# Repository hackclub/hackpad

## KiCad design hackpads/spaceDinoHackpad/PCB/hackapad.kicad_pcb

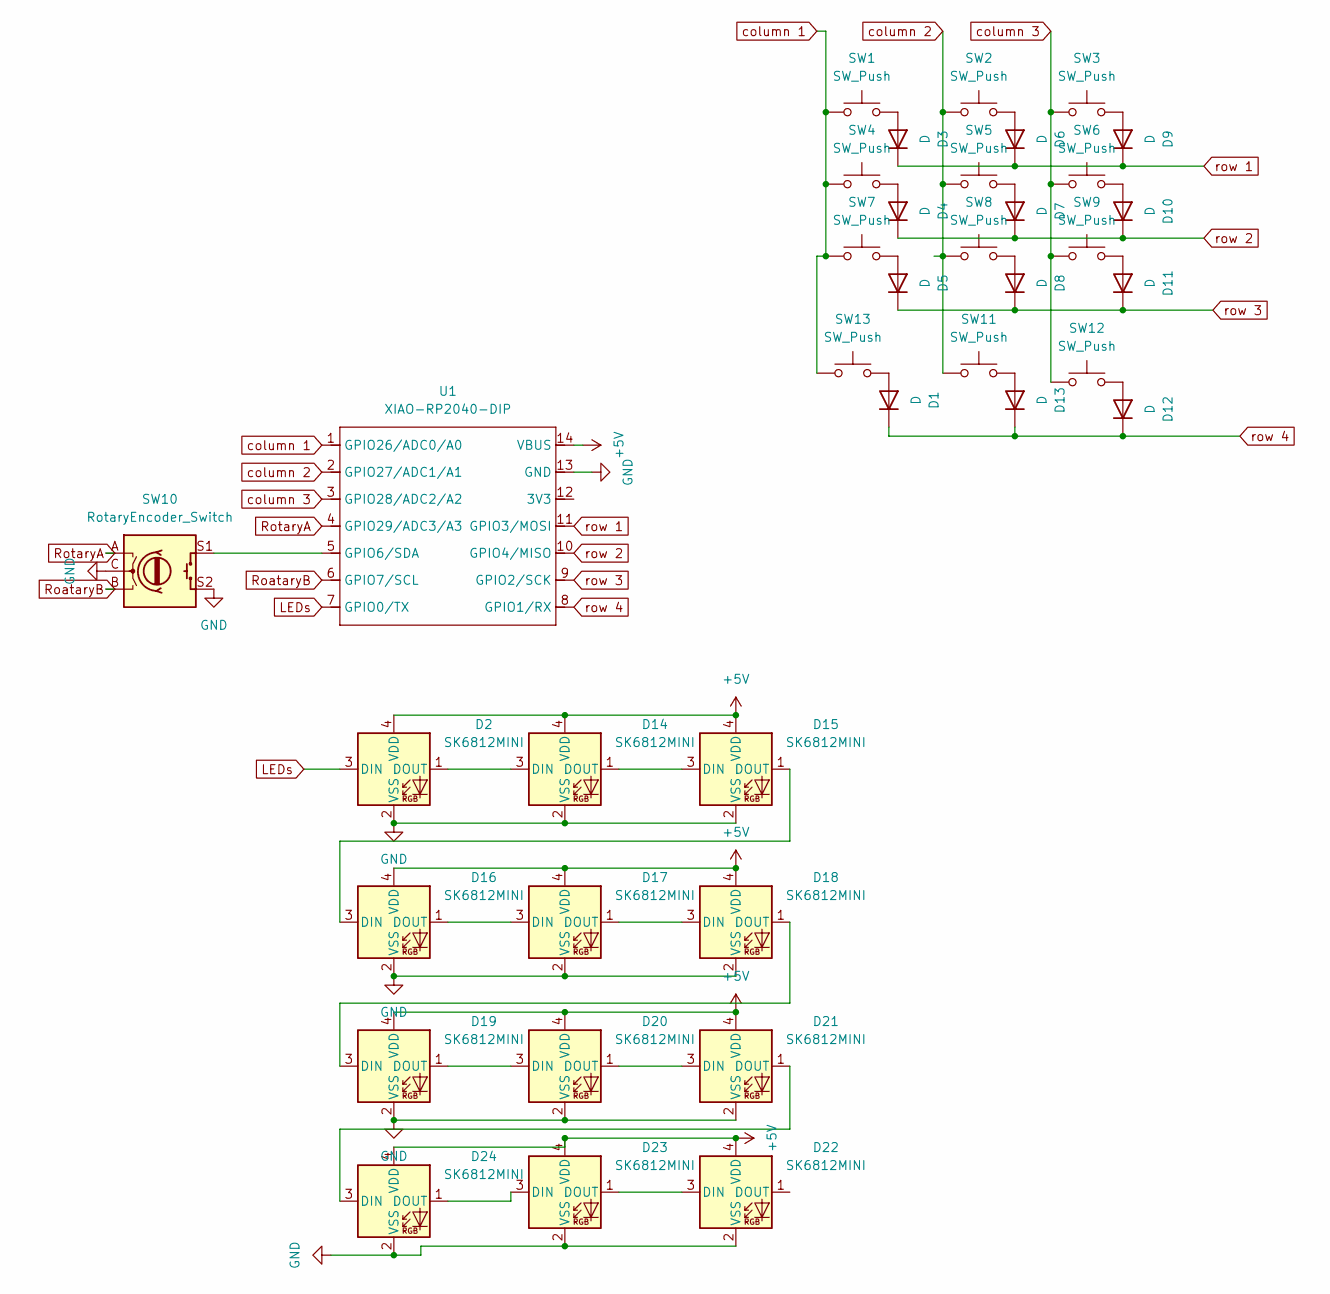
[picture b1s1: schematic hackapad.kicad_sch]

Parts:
D1, D3, D4, D5, D6, D7, D8, D9, D10, D11, D12, D13: D; D_DO-35_SOD27_P7.62mm_Horizontal
D2, D14, D15, D16, D17, D18, D19, D20, D21, D22, D23, D24: SK6812MINI; SK6812MINI-E
SW1, SW2, SW3, SW4, SW5, SW6, SW7, SW8, SW9, SW11, SW12, SW13: SW_Push; SW_Cherry_MX_1.00u_PCB_copy
SW10: RotaryEncoder_Switch; RotaryEncoder_Alps_EC11E-Switch_Vertical_H20mm_CircularMoun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
U1: XIAO-RP2040-DIP

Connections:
+5V: D2.4 (VDD), D14.4 (VDD), D15.4 (VDD), D16.4 (VDD), D17.4 (VDD), D18.4 (VDD), D19.4 (VDD), D20.4 (VDD), D21.4 (VDD), D22.4 (VDD), D23.4 (VDD), D24.4 (VDD), U1.14 (VBUS)
GND: D2.2 (VSS), D14.2 (VSS), D15.2 (VSS), D16.2 (VSS), D17.2 (VSS), D18.2 (VSS), D19.2 (VSS), D20.2 (VSS), D21.2 (VSS), D22.2 (VSS), D23.2 (VSS), D24.2 (VSS), SW10.C, SW10.S2, U1.13 (GND)
LEDs: D2.3 (DIN), U1.7 (GPIO0/TX)
unnamed: D1.2 (A), SW13.2
unnamed: D3.2 (A), SW1.2
unnamed: D4.2 (A), SW4.2
unnamed: D5.2 (A), SW7.2
unnamed: D6.2 (A), SW2.2
unnamed: D7.2 (A), SW5.2
unnamed: D8.2 (A), SW8.2
unnamed: D9.2 (A), SW3.2
unnamed: D10.2 (A), SW6.2
unnamed: D11.2 (A), SW9.2
unnamed: D12.2 (A), SW12.2
unnamed: D13.2 (A), SW11.2
unnamed: D2.1 (DOUT), D14.3 (DIN)
unnamed: D14.1 (DOUT), D15.3 (DIN)
unnamed: D15.1 (DOUT), D16.3 (DIN)
unnamed: D16.1 (DOUT), D17.3 (DIN)
unnamed: D17.1 (DOUT), D18.3 (DIN)
unnamed: D18.1 (DOUT), D19.3 (DIN)
unnamed: D19.1 (DOUT), D20.3 (DIN)
unnamed: D20.1 (DOUT), D21.3 (DIN)
unnamed: D21.1 (DOUT), D24.3 (DIN)
unnamed: D22.3 (DIN), D23.1 (DOUT)
unnamed: D23.3 (DIN), D24.1 (DOUT)
unnamed: SW10.S1, U1.5 (GPIO6/SDA)
RoataryB: SW10.B, U1.6 (GPIO7/SCL)
RotaryA: SW10.A, U1.4 (GPIO29/ADC3/A3)
column 1: SW1.1, SW4.1, SW7.1, SW13.1, U1.1 (GPIO26/ADC0/A0)
column 2: SW2.1, SW5.1, SW8.1, SW11.1, U1.2 (GPIO27/ADC1/A1)
column 3: SW3.1, SW6.1, SW9.1, SW12.1, U1.3 (GPIO28/ADC2/A2)
row 1: D3.1 (K), D6.1 (K), D9.1 (K), U1.11 (GPIO3/MOSI)
row 2: D4.1 (K), D7.1 (K), D10.1 (K), U1.10 (GPIO4/MISO)
row 3: D5.1 (K), D8.1 (K), D11.1 (K), U1.9 (GPIO2/SCK)
row 4: D1.1 (K), D12.1 (K), D13.1 (K), U1.8 (GPIO1/RX)

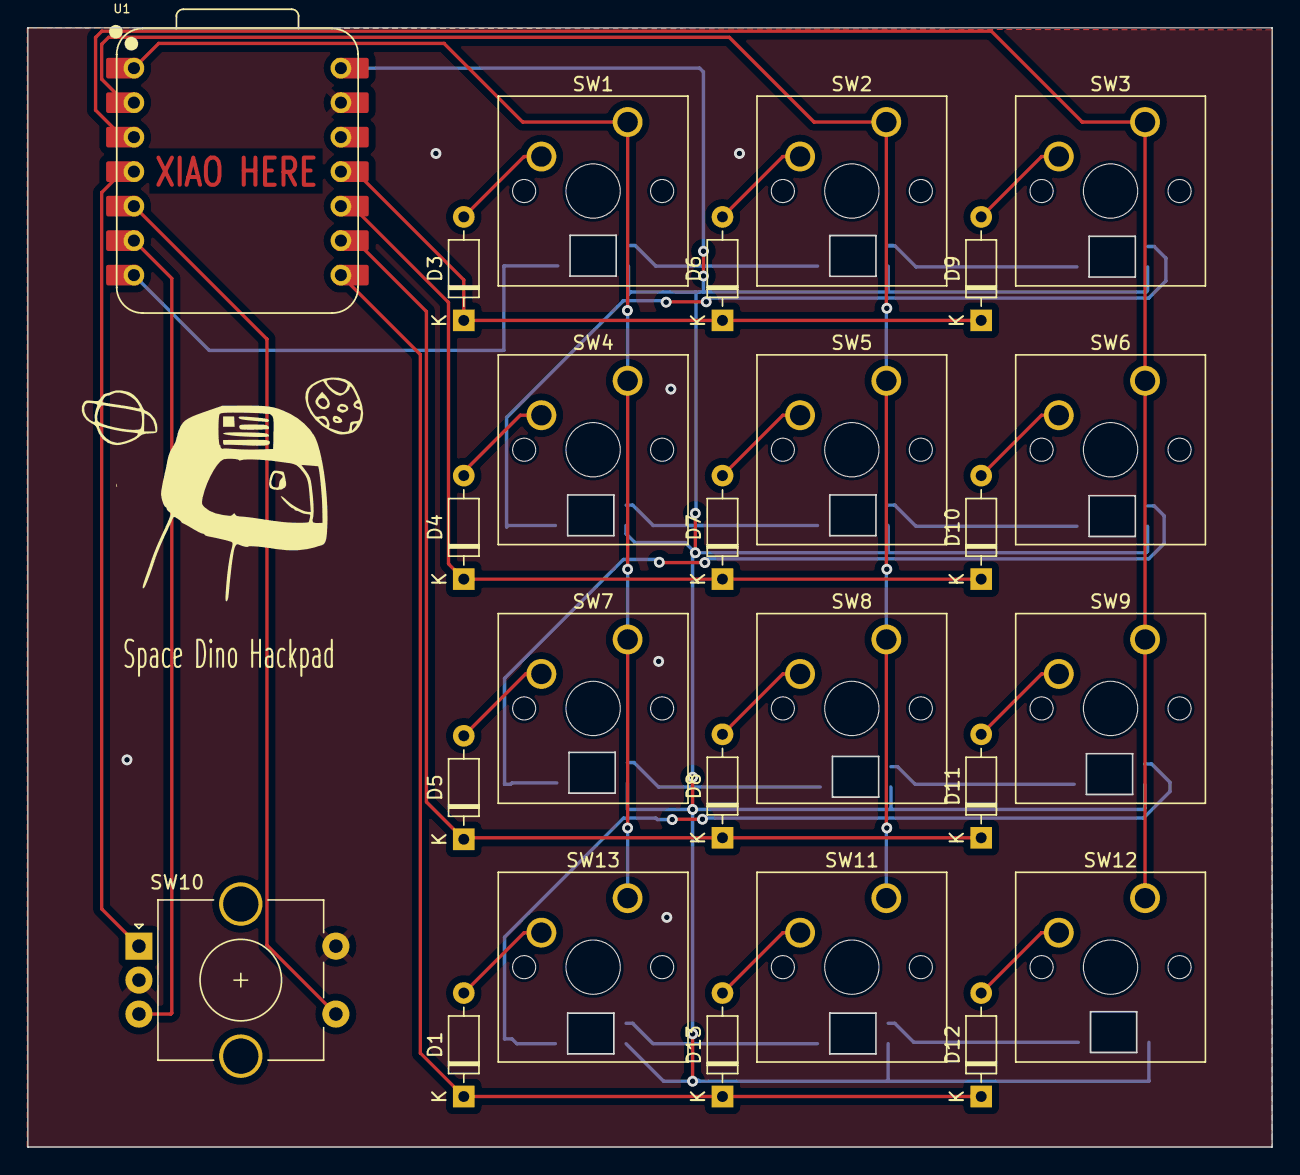
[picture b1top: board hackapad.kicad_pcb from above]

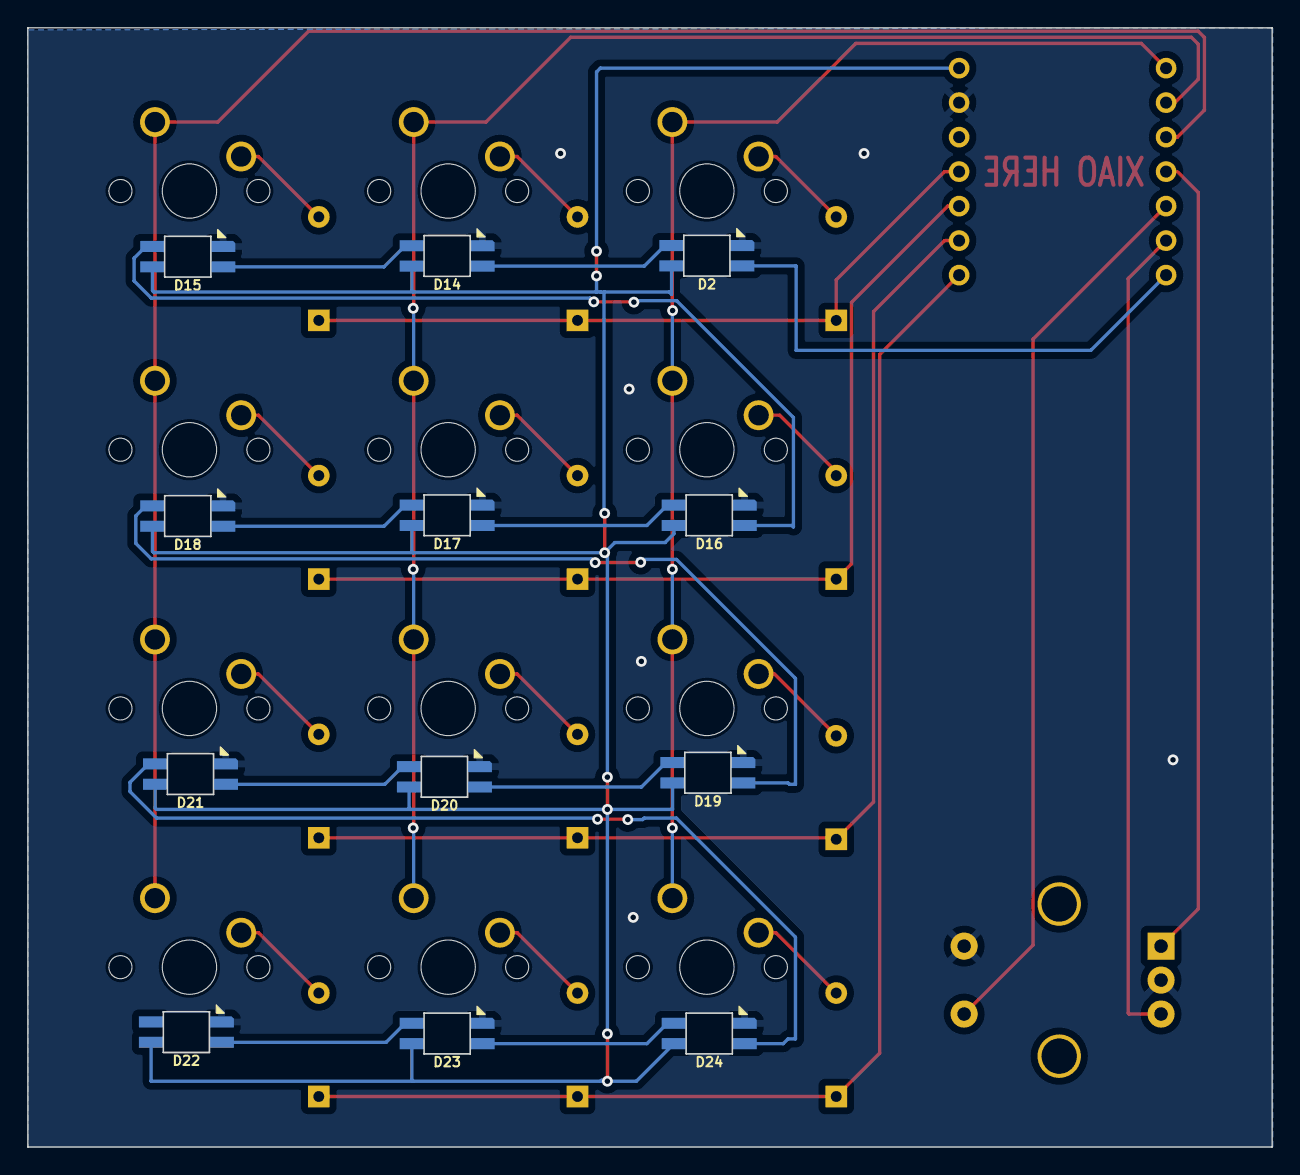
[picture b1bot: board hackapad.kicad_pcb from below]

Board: 2 copper layers, 91.6 x 82.4 mm, 38 parts (12 on the bottom side), 36 nets.

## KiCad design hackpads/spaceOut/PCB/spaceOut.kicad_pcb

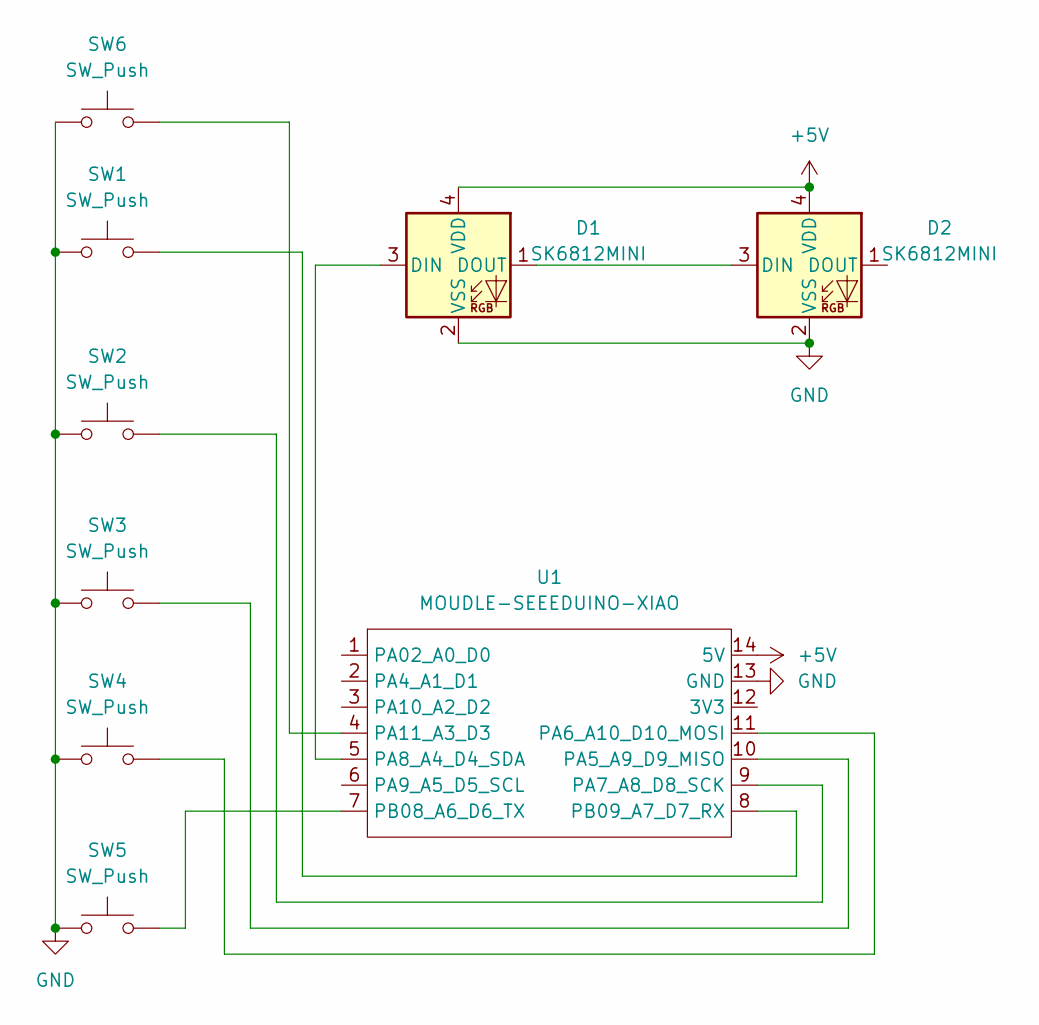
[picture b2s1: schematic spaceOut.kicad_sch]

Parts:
D1, D2: SK6812MINI; LED_SK6812MINI_PLCC4_3.5x3.5mm_P1.75mm
SW1, SW2, SW3, SW4, SW6: SW_Push; SW_Cherry_MX_1.00u_PCB
SW5: SW_Push; SW_Cherry_MX_2.75u_PCB
U1: MOUDLE-SEEEDUINO-XIAO; XIAO-SAMD21-RP2040-14P-2.54-21X17.8MM (Seeeduino XIAO)

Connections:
+5V: D1.4 (VDD), D2.4 (VDD), U1.14 (5V)
GND: D1.2 (VSS), D2.2 (VSS), SW1.1, SW2.1, SW3.1, SW4.1, SW5.1, SW6.1, U1.13 (GND)
unnamed: D1.3 (DIN), U1.5 (PA8_A4_D4_SDA)
unnamed: D1.1 (DOUT), D2.3 (DIN)
unnamed: SW3.2, U1.10 (PA5_A9_D9_MISO)
unnamed: SW4.2, U1.11 (PA6_A10_D10_MOSI)
unnamed: SW2.2, U1.9 (PA7_A8_D8_SCK)
unnamed: SW6.2, U1.4 (PA11_A3_D3)
unnamed: SW5.2, U1.7 (PB08_A6_D6_TX)
unnamed: SW1.2, U1.8 (PB09_A7_D7_RX)

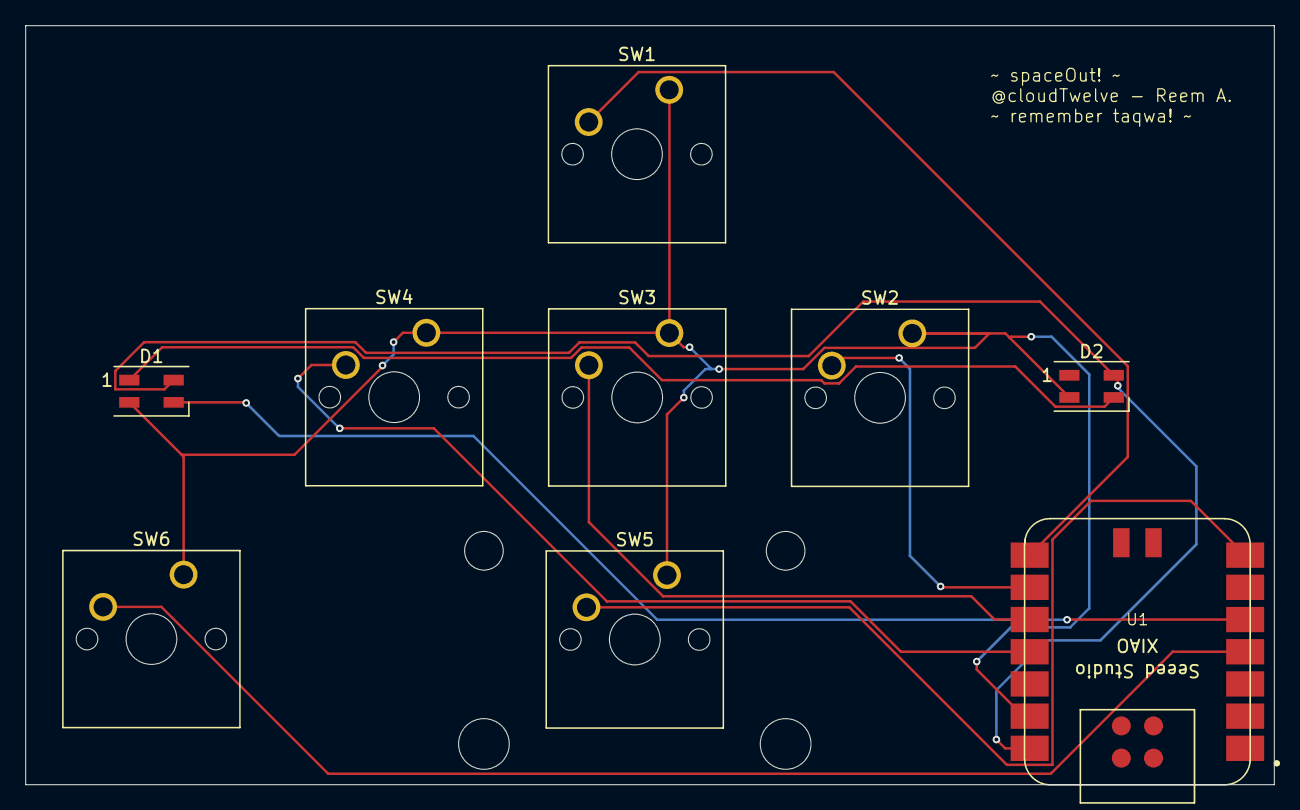
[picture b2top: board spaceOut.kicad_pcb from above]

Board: 2 copper layers, 98.5 x 59.9 mm, 9 parts (0 on the bottom side), 10 nets.

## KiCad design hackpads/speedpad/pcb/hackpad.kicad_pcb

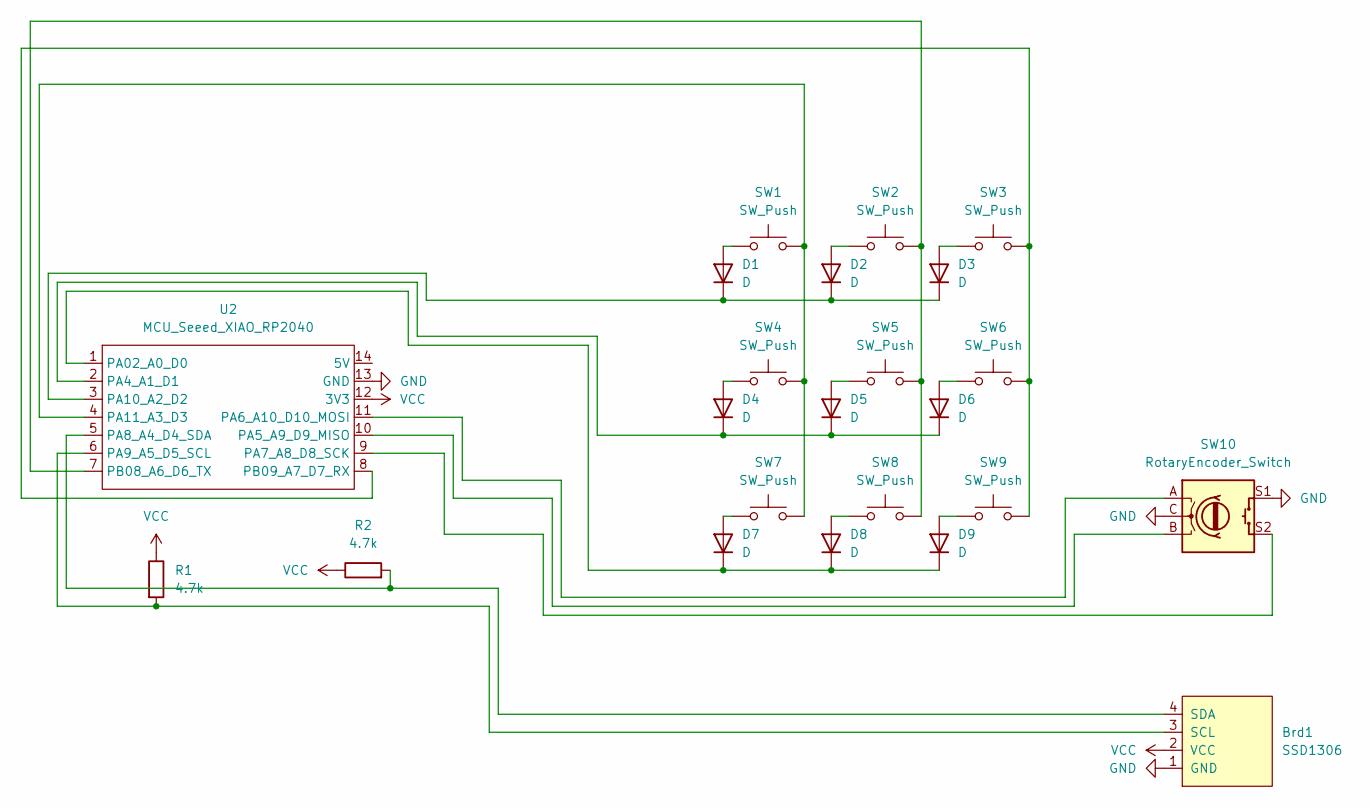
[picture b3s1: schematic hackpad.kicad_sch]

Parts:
Brd1: SSD1306; SSD1306-0.91-OLED-4pin-128x32
D1, D2, D3, D4, D5, D6, D7, D8, D9: D; DIODE-1N4148
R1, R2: 4.7k; R_Axial_DIN0204_L3.6mm_D1.6mm_P5.08mm_Horizontal
SW1, SW2, SW3, SW4, SW5, SW6, SW7, SW8, SW9: SW_Push; SW_Cherry_MX_1.00u_PCB
SW10: RotaryEncoder_Switch; RotaryEncoder_Alps_EC11E-Switch_Vertical_H20mm
U2: MCU_Seeed_XIAO_RP2040; XIAO-RP2040

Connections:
GND: Brd1.1 (GND), SW10.C, SW10.S1, U2.13 (GND)
unnamed: Brd1.3 (SCL), R1.2, U2.6 (PA9_A5_D5_SCL)
unnamed: Brd1.4 (SDA), R2.2, U2.5 (PA8_A4_D4_SDA)
unnamed: D1.A, SW1.1
unnamed: D2.A, SW2.1
unnamed: D3.A, SW3.1
unnamed: D4.A, SW4.1
unnamed: D5.A, SW5.1
unnamed: D6.A, SW6.1
unnamed: D7.A, SW7.1
unnamed: D8.A, SW8.1
unnamed: D9.A, SW9.1
unnamed: D7.K, D8.K, D9.K, U2.1 (PA02_A0_D0)
unnamed: D4.K, D5.K, D6.K, U2.2 (PA4_A1_D1)
unnamed: SW10.B, U2.10 (PA5_A9_D9_MISO)
unnamed: SW10.A, U2.11 (PA6_A10_D10_MOSI)
unnamed: SW10.S2, U2.9 (PA7_A8_D8_SCK)
unnamed: D1.K, D2.K, D3.K, U2.3 (PA10_A2_D2)
unnamed: SW1.2, SW4.2, SW7.2, U2.4 (PA11_A3_D3)
unnamed: SW2.2, SW5.2, SW8.2, U2.7 (PB08_A6_D6_TX)
unnamed: SW3.2, SW6.2, SW9.2, U2.8 (PB09_A7_D7_RX)
VCC: Brd1.2 (VCC), R1.1, R2.1, U2.12 (3V3)

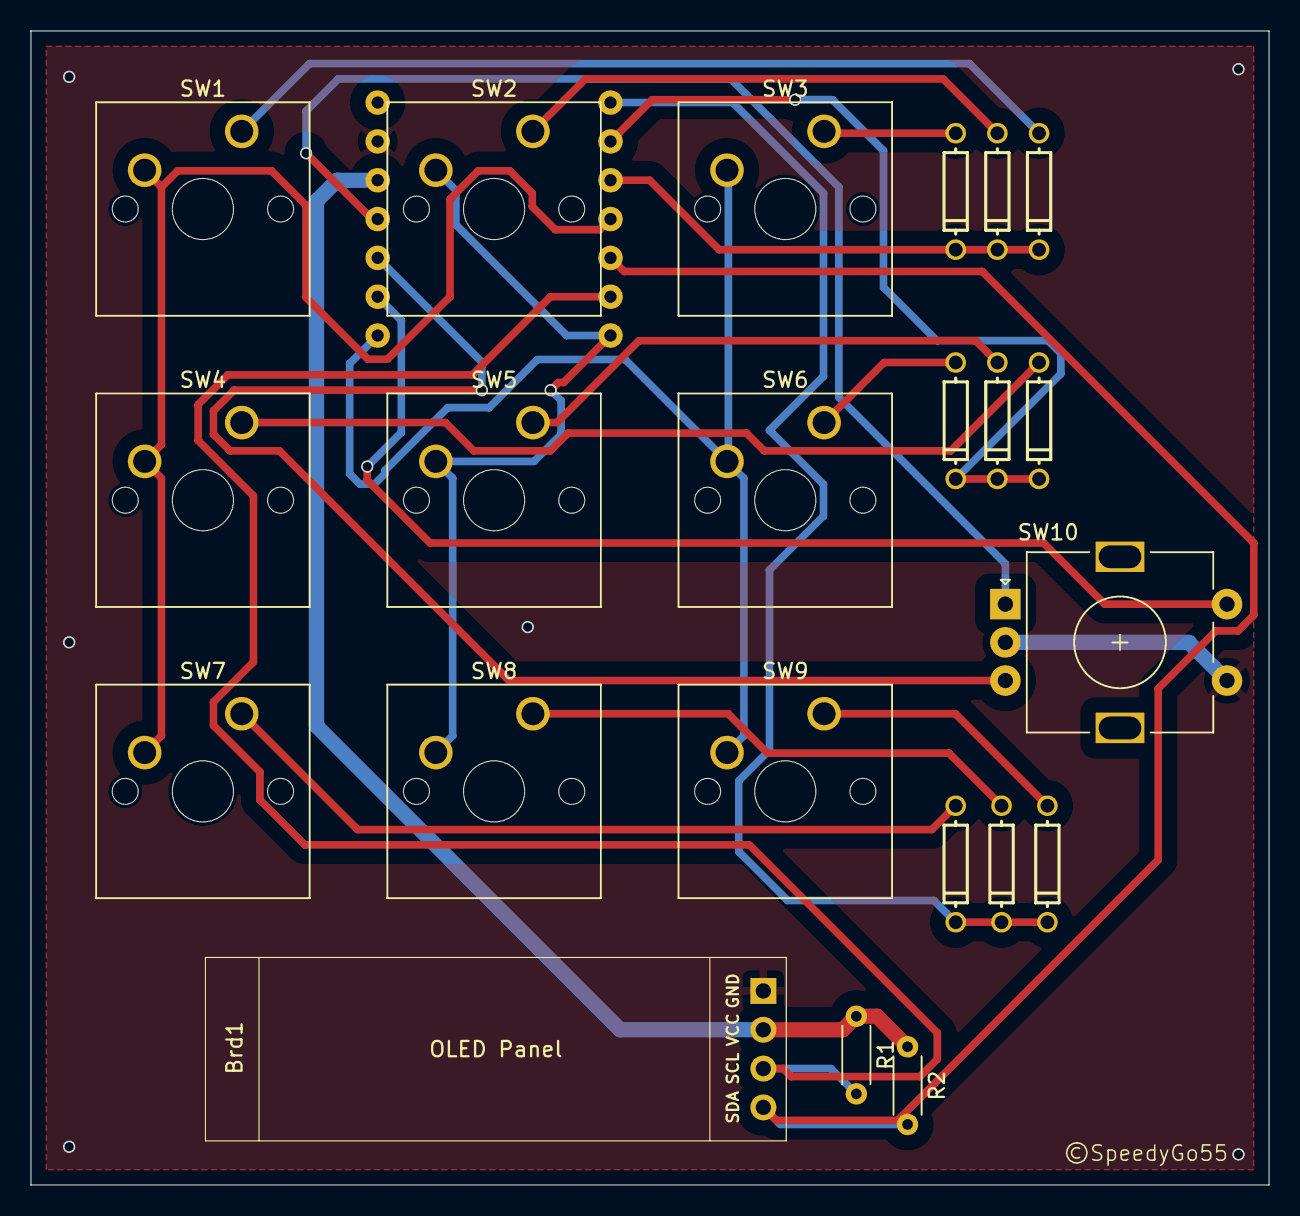
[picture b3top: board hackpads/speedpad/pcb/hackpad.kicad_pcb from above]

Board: 2 copper layers, 81.0 x 75.5 mm, 23 parts (1 on the bottom side), 22 nets.

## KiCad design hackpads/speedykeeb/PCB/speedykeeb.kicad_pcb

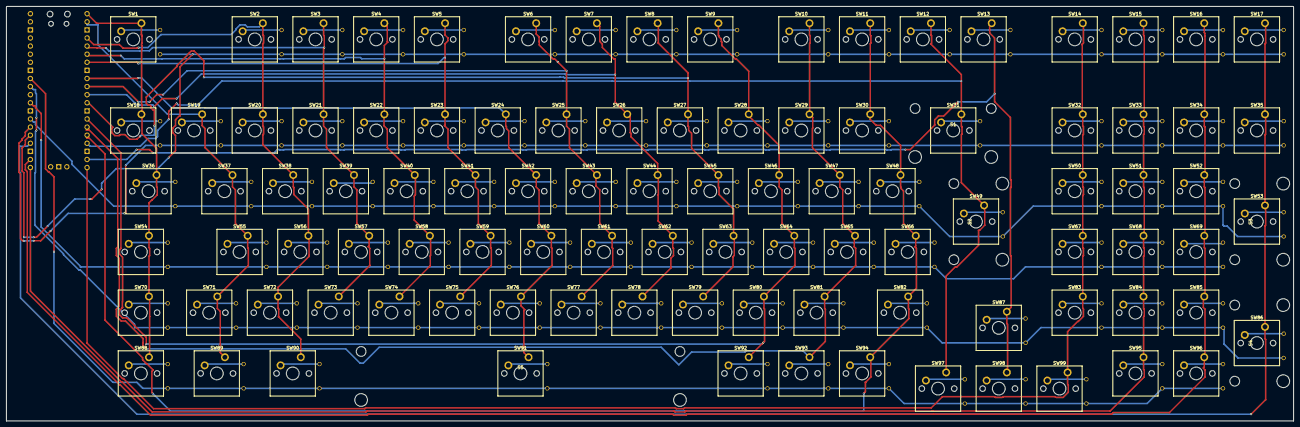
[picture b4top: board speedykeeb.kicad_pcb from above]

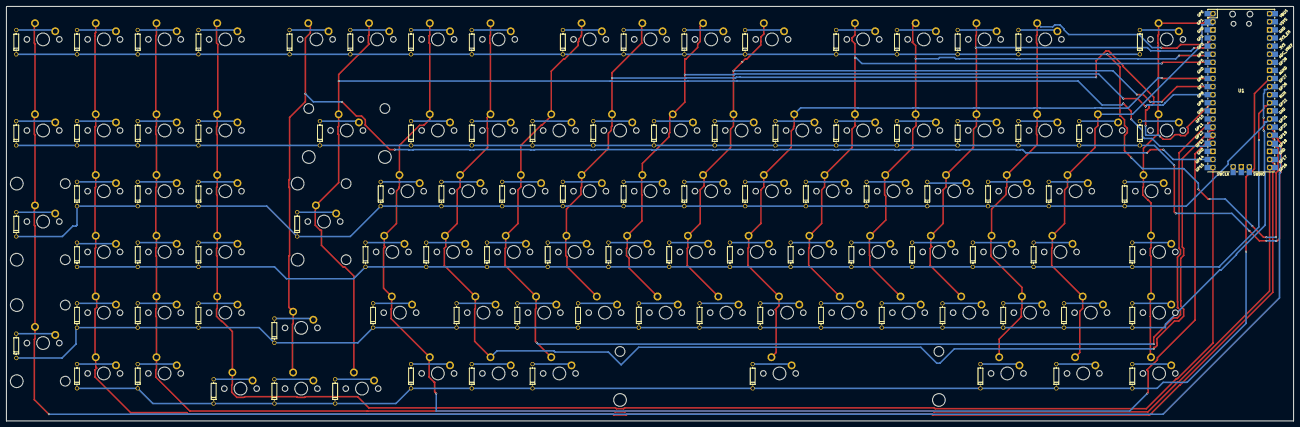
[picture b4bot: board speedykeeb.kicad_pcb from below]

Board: 2 copper layers, 403.7 x 130.0 mm, 204 parts (100 on the bottom side), 124 nets.

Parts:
D1, D2, D3, D4, D5, D6, D7, D8, D9, D10, D11, D12, D13, D14, D15, D16, D17, D18, D19, D20, D21, D22, D23, D24, D25, D26, D27, D28, D29, D30, D31, D32, D33, D34, D35, D36, D37, D38, D39, D40, D41, D42, D43, D44, D45, D46, D47, D48, D49, D50, D51, D52, D53, D54, D55, D56, D57, D58, D59, D60, D61, D62, D63, D64, D65, D66, D67, D68, D69, D70, D71, D72, D73, D74, D75, D76, D77, D78, D79, D80, D81, D82, D83, D84, D85, D86, D87, D88, D89, D90, D91, D92, D93, D94, D95, D96, D97, D98, D99: D; DIODE-1N4148 (1)
S1, S2, S3, S4: Stabilizer_Cherry_MX_2.00u
S5: Stabilizer_Cherry_MX_6.25u
SW1, SW2, SW3, SW4, SW5, SW6, SW7, SW8, SW9, SW10, SW11, SW12, SW13, SW14, SW15, SW16, SW17, SW18, SW19, SW20, SW21, SW22, SW23, SW24, SW25, SW26, SW27, SW28, SW29, SW30, SW31, SW32, SW33, SW34, SW35, SW36, SW37, SW38, SW39, SW40, SW41, SW42, SW43, SW44, SW45, SW46, SW47, SW48, SW49, SW50, SW51, SW52, SW53, SW54, SW55, SW56, SW57, SW58, SW59, SW60, SW61, SW62, SW63, SW64, SW65, SW66, SW67, SW68, SW69, SW70, SW71, SW72, SW73, SW74, SW75, SW76, SW77, SW78, SW79, SW80, SW81, SW82, SW83, SW84, SW85, SW86, SW87, SW88, SW89, SW90, SW91, SW92, SW93, SW94, SW95, SW96, SW97, SW98, SW99: SW_Push; SW_Cherry_MX_PCB_1.00u
U1: Pico; RPi_Pico_SMD_TH

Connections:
Col0: SW1.2, SW18.2, SW36.2, SW54.2, SW70.2, SW88.2, U1.1 (GPIO0)
Col1: SW19.2, SW37.2, SW55.2, SW71.2, SW89.2, U1.2 (GPIO1)
Col2: SW2.2, SW20.2, SW38.2, SW56.2, SW72.2, SW90.2, U1.4 (GPIO2)
Col3: SW3.2, SW21.2, SW39.2, SW57.2, SW73.2, U1.5 (GPIO3)
Col4: SW4.2, SW22.2, SW40.2, SW58.2, SW74.2, U1.6 (GPIO4)
Col5: SW5.2, SW23.2, SW41.2, SW59.2, SW75.2, U1.7 (GPIO5)
Col6: SW24.2, SW42.2, SW60.2, SW76.2, SW91.2, U1.9 (GPIO6)
Col7: SW6.2, SW25.2, SW43.2, SW61.2, SW77.2, U1.10 (GPIO7)
Col8: SW7.2, SW26.2, SW44.2, SW62.2, SW78.2, U1.11 (GPIO8)
Col9: SW8.2, SW27.2, SW45.2, SW63.2, SW79.2, U1.12 (GPIO9)
Col10: SW9.2, SW28.2, SW46.2, SW64.2, SW80.2, SW92.2, U1.14 (GPIO10)
Col11: SW10.2, SW29.2, SW47.2, SW65.2, SW81.2, SW93.2, U1.15 (GPIO11)
Col12: SW11.2, SW30.2, SW48.2, SW66.2, SW82.2, SW94.2, U1.16 (GPIO12)
Col13: SW12.2, SW31.2, SW49.2, SW97.2, U1.17 (GPIO13)
Col14: SW13.2, SW87.2, SW98.2, U1.19 (GPIO14)
Col15: SW14.2, SW32.2, SW50.2, SW67.2, SW83.2, SW99.2, U1.20 (GPIO15)
Col16: SW15.2, SW33.2, SW51.2, SW68.2, SW84.2, SW95.2, U1.21 (GPIO16)
Col17: SW16.2, SW34.2, SW52.2, SW69.2, SW85.2, SW96.2, U1.22 (GPIO17)
Col18: SW17.2, SW35.2, SW53.2, SW86.2, U1.24 (GPIO18)
unnamed: D1.A, SW1.1
unnamed: D2.A, SW2.1
unnamed: D3.A, SW3.1
unnamed: D4.A, SW4.1
unnamed: D5.A, SW5.1
unnamed: D6.A, SW6.1
unnamed: D7.A, SW7.1
unnamed: D8.A, SW8.1
unnamed: D9.A, SW9.1
unnamed: D10.A, SW10.1
unnamed: D11.A, SW11.1
unnamed: D12.A, SW12.1
unnamed: D13.A, SW13.1
unnamed: D14.A, SW14.1
unnamed: D15.A, SW15.1
unnamed: D16.A, SW16.1
unnamed: D17.A, SW17.1
unnamed: D18.A, SW18.1
unnamed: D19.A, SW19.1
unnamed: D20.A, SW20.1
unnamed: D21.A, SW21.1
unnamed: D22.A, SW22.1
unnamed: D23.A, SW23.1
unnamed: D24.A, SW24.1
unnamed: D25.A, SW25.1
unnamed: D26.A, SW26.1
unnamed: D27.A, SW27.1
unnamed: D28.A, SW28.1
unnamed: D29.A, SW29.1
unnamed: D30.A, SW30.1
unnamed: D31.A, SW31.1
unnamed: D32.A, SW32.1
unnamed: D33.A, SW33.1
unnamed: D34.A, SW34.1
unnamed: D35.A, SW35.1
unnamed: D36.A, SW36.1
unnamed: D37.A, SW37.1
unnamed: D38.A, SW38.1
unnamed: D39.A, SW39.1
unnamed: D40.A, SW40.1
unnamed: D41.A, SW41.1
unnamed: D42.A, SW42.1
unnamed: D43.A, SW43.1
unnamed: D44.A, SW44.1
unnamed: D45.A, SW45.1
unnamed: D46.A, SW46.1
unnamed: D47.A, SW47.1
unnamed: D48.A, SW48.1
unnamed: D49.A, SW49.1
unnamed: D50.A, SW50.1
unnamed: D51.A, SW51.1
unnamed: D52.A, SW52.1
unnamed: D53.A, SW53.1
unnamed: D54.A, SW54.1
unnamed: D55.A, SW55.1
unnamed: D56.A, SW56.1
unnamed: D57.A, SW57.1
unnamed: D58.A, SW58.1
unnamed: D59.A, SW59.1
unnamed: D60.A, SW60.1
unnamed: D61.A, SW61.1
unnamed: D62.A, SW62.1
unnamed: D63.A, SW63.1
unnamed: D64.A, SW64.1
unnamed: D65.A, SW65.1
unnamed: D66.A, SW66.1
unnamed: D67.A, SW67.1
unnamed: D68.A, SW68.1
unnamed: D69.A, SW69.1
unnamed: D70.A, SW70.1
unnamed: D71.A, SW71.1
unnamed: D72.A, SW72.1
unnamed: D73.A, SW73.1
unnamed: D74.A, SW74.1
unnamed: D75.A, SW75.1
unnamed: D76.A, SW76.1
unnamed: D77.A, SW77.1
unnamed: D78.A, SW78.1
unnamed: D79.A, SW79.1
unnamed: D80.A, SW80.1
unnamed: D81.A, SW81.1
unnamed: D82.A, SW82.1
unnamed: D83.A, SW83.1
unnamed: D84.A, SW84.1
unnamed: D85.A, SW85.1
unnamed: D86.A, SW86.1
unnamed: D87.A, SW87.1
unnamed: D88.A, SW88.1
unnamed: D89.A, SW89.1
unnamed: D90.A, SW90.1
unnamed: D91.A, SW91.1
unnamed: D92.A, SW92.1
unnamed: D93.A, SW93.1
unnamed: D94.A, SW94.1
unnamed: D95.A, SW95.1
unnamed: D96.A, SW96.1
unnamed: D97.A, SW97.1
unnamed: D98.A, SW98.1
unnamed: D99.A, SW99.1
Row0: D1.K, D2.K, D3.K, D4.K, D5.K, D6.K, D7.K, D8.K, D9.K, D10.K, D11.K, D12.K, D13.K, D14.K, D15.K, D16.K, D17.K, U1.25 (GPIO19)
Row1: D18.K, D19.K, D20.K, D21.K, D22.K, D23.K, D24.K, D25.K, D26.K, D27.K, D28.K, D29.K, D30.K, D31.K, D32.K, D33.K, D34.K, D35.K, U1.26 (GPIO20)
Row2: D36.K, D37.K, D38.K, D39.K, D40.K, D41.K, D42.K, D43.K, D44.K, D45.K, D46.K, D47.K, D48.K, D49.K, D50.K, D51.K, D52.K, D53.K, U1.27 (GPIO21)
Row3: D54.K, D55.K, D56.K, D57.K, D58.K, D59.K, D60.K, D61.K, D62.K, D63.K, D64.K, D65.K, D66.K, D67.K, D68.K, D69.K, U1.29 (GPIO22)
Row4: D70.K, D71.K, D72.K, D73.K, D74.K, D75.K, D76.K, D77.K, D78.K, D79.K, D80.K, D81.K, D82.K, D83.K, D84.K, D85.K, D86.K, D87.K, U1.31 (GPIO26_ADC0)
Row5: D88.K, D89.K, D90.K, D91.K, D92.K, D93.K, D94.K, D95.K, D96.K, D97.K, D98.K, D99.K, U1.32 (GPIO27_ADC1)

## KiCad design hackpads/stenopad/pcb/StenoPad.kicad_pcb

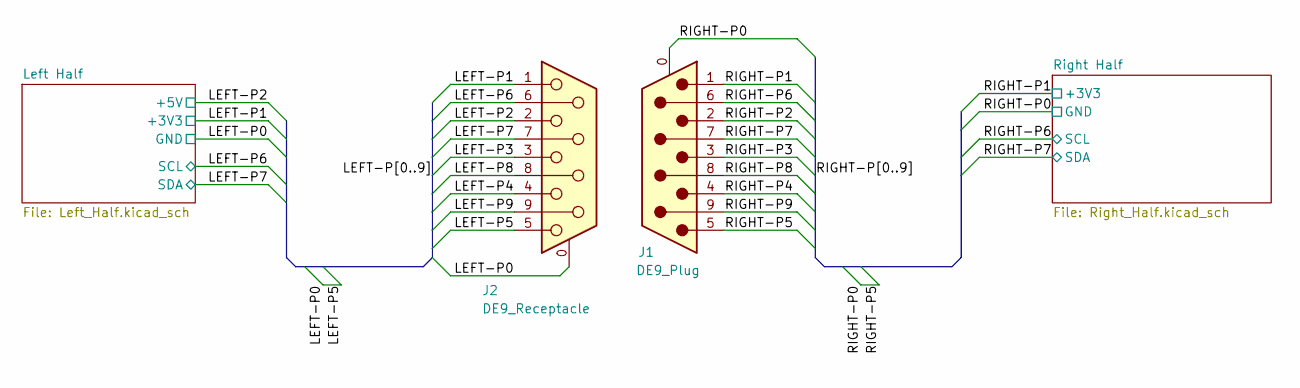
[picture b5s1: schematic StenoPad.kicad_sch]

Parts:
J1: DE9_Plug; DSUB-9_Male_Horizontal_P2.77x2.84mm_EdgePinOffset4.94mm_Hou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
J2: DE9_Receptacle; DSUB-9_Female_Horizontal_P2.77x2.84mm_EdgePinOffset4.94mm_H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

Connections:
/LEFT-P1: J2.1; also elsewhere on the board
/LEFT-P2: J2.2; also elsewhere on the board
/LEFT-P3: J2.3; also elsewhere on the board
/LEFT-P4: J2.4
/LEFT-P5: J2.0 (PAD), J2.5; also elsewhere on the board
/LEFT-P6: J2.6; also elsewhere on the board
/LEFT-P7: J2.7; also elsewhere on the board
/LEFT-P8: J2.8
/LEFT-P9: J2.9
/RIGHT-P0: J1.0 (PAD), J1.5; also elsewhere on the board
/RIGHT-P1: J1.1; also elsewhere on the board
/RIGHT-P2: J1.2
/RIGHT-P3: J1.3; also elsewhere on the board
/RIGHT-P4: J1.4
/RIGHT-P6: J1.6; also elsewhere on the board
/RIGHT-P7: J1.7; also elsewhere on the board
/RIGHT-P8: J1.8
/RIGHT-P9: J1.9

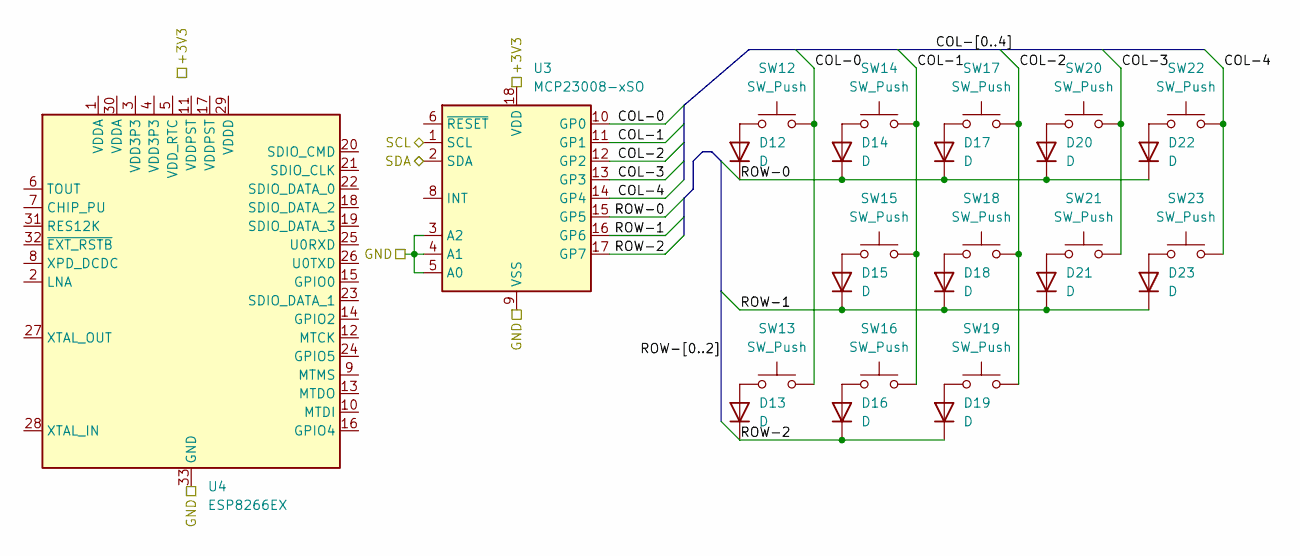
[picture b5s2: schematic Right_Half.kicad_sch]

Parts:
D12, D13, D14, D15, D16, D17, D18, D19, D20, D21, D22, D23: D; D_0603_1608Metric
SW12: SW_Push; MX-Hotswap-2U-Vertical-ReversedStabilizers
SW13, SW14, SW15, SW16, SW17, SW18, SW19, SW20, SW21, SW22, SW23: SW_Push; MX-Hotswap-1U
U3: MCP23008-xSO; SOIC-18W_7.5x11.6mm_P1.27mm
U4: ESP8266EX; QFN-32-1EP_5x5mm_P0.5mm_EP3.45x3.45mm

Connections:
/RIGHT-P0: U3.3 (A2), U3.4 (A1), U3.5 (A0), U3.9 (VSS), U4.9 (GND), U4.13 (GND), U4.18 (GND), U4.19 (GND), U4.33 (GND); also elsewhere on the board
/RIGHT-P1: U3.18 (VDD), U4.1 (VDD); also elsewhere on the board
/RIGHT-P3: U4.15 (RST); also elsewhere on the board
/RIGHT-P6: U4.12 (TXD); also elsewhere on the board
/RIGHT-P7: U4.11 (RXD); also elsewhere on the board
/Right Half/COL-0: SW12.2, SW13.2, U3.10 (GP0)
/Right Half/COL-1: SW14.2, SW15.2, SW16.2, U3.11 (GP1)
/Right Half/COL-2: SW17.2, SW18.2, SW19.2, U3.12 (GP2)
/Right Half/COL-3: SW20.2, SW21.2, U3.13 (GP3)
/Right Half/COL-4: SW22.2, SW23.2, U3.14 (GP4)
/Right Half/ROW-0: D12.1 (K), D14.1 (K), D17.1 (K), D20.1 (K), D22.1 (K), U3.15 (GP5)
/Right Half/ROW-1: D15.1 (K), D18.1 (K), D21.1 (K), D23.1 (K), U3.16 (GP6)
/Right Half/ROW-2: D13.1 (K), D16.1 (K), D19.1 (K), U3.17 (GP7)
unnamed: D12.2 (A), SW12.1
unnamed: D13.2 (A), SW13.1
unnamed: D14.2 (A), SW14.1
unnamed: D15.2 (A), SW15.1
unnamed: D16.2 (A), SW16.1
unnamed: D17.2 (A), SW17.1
unnamed: D18.2 (A), SW18.1
unnamed: D19.2 (A), SW19.1
unnamed: D20.2 (A), SW20.1
unnamed: D21.2 (A), SW21.1
unnamed: D22.2 (A), SW22.1
unnamed: D23.2 (A), SW23.1
unnamed: U3.1 (SCL), U4.3 (IO14)
unnamed: U3.2 (SDA), U4.7 (IO2)

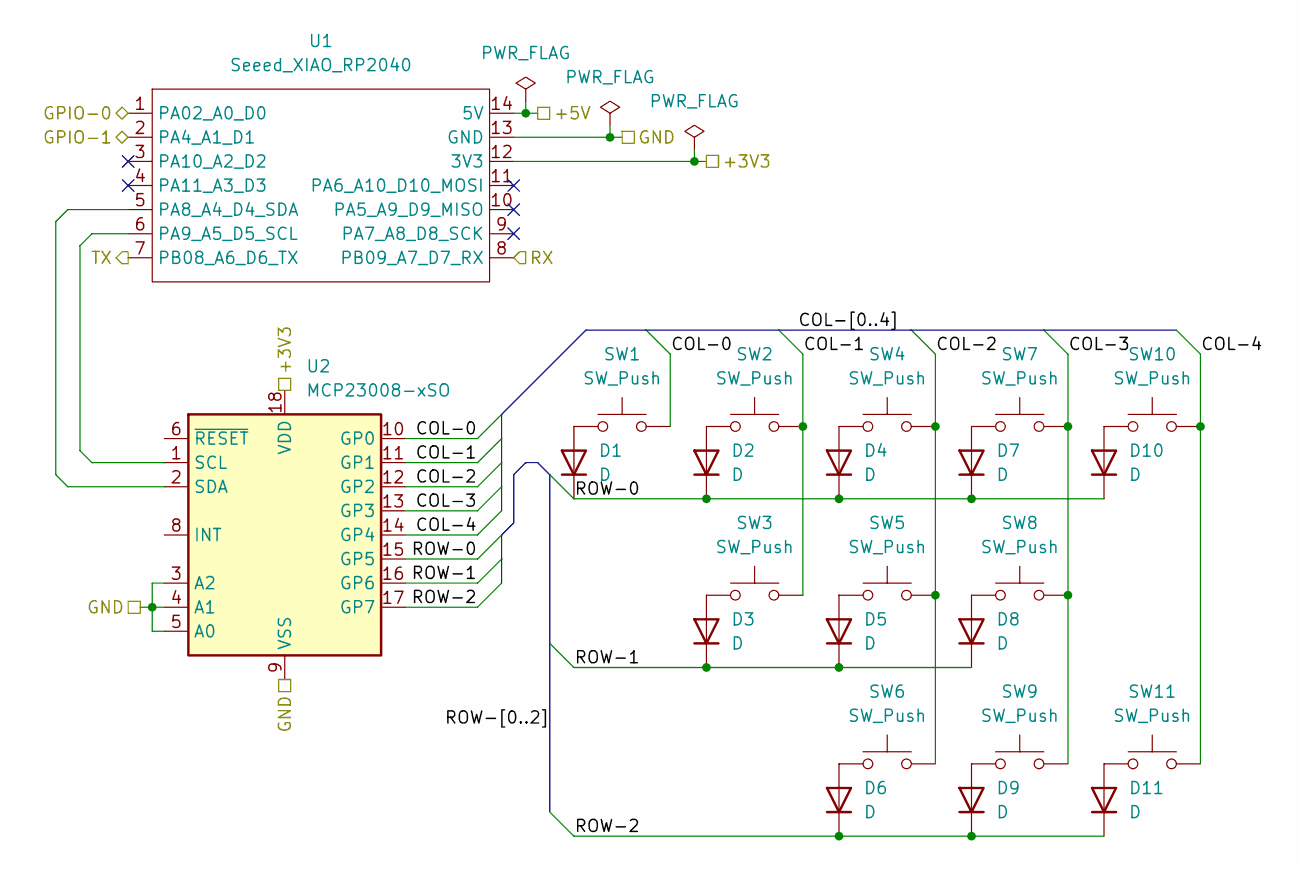
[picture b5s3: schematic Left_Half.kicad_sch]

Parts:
D1, D2, D3, D4, D5, D6, D7, D8, D9, D10, D11: D; D_0603_1608Metric
SW1: SW_Push; MX-Hotswap-2U-Vertical-ReversedStabilizers
SW2, SW3, SW4, SW5, SW6, SW7, SW8, SW9, SW11: SW_Push; MX-Hotswap-1U
SW10: SW_Push; MX-Hotswap-2U-Vertical
U1: Seeed_XIAO_RP2040; MOUDLE14P-2.54-21X17.8MM
U2: MCP23008-xSO; SOIC-18W_7.5x11.6mm_P1.27mm

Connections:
/LEFT-P1: U1.12 (3V3), U2.18 (VDD); also elsewhere on the board
/LEFT-P2: U1.14 (5V); also elsewhere on the board
/LEFT-P3: U1.1 (PA02_A0_D0); also elsewhere on the board
/LEFT-P5: U1.13 (GND), U2.3 (A2), U2.4 (A1), U2.5 (A0), U2.9 (VSS); also elsewhere on the board
/LEFT-P6: U1.8 (PB09_A7_D7_RX); also elsewhere on the board
/LEFT-P7: U1.7 (PB08_A6_D6_TX); also elsewhere on the board
/Left Half/COL-0: SW1.2, U2.10 (GP0)
/Left Half/COL-1: SW2.2, SW3.2, U2.11 (GP1)
/Left Half/COL-2: SW4.2, SW5.2, SW6.2, U2.12 (GP2)
/Left Half/COL-3: SW7.2, SW8.2, SW9.2, U2.13 (GP3)
/Left Half/COL-4: SW10.2, SW11.2, U2.14 (GP4)
/Left Half/ROW-0: D1.1 (K), D2.1 (K), D4.1 (K), D7.1 (K), D10.1 (K), U2.15 (GP5)
/Left Half/ROW-1: D3.1 (K), D5.1 (K), D8.1 (K), U2.16 (GP6)
/Left Half/ROW-2: D6.1 (K), D9.1 (K), D11.1 (K), U2.17 (GP7)
unnamed: D1.2 (A), SW1.1
unnamed: D2.2 (A), SW2.1
unnamed: D3.2 (A), SW3.1
unnamed: D4.2 (A), SW4.1
unnamed: D5.2 (A), SW5.1
unnamed: D6.2 (A), SW6.1
unnamed: D7.2 (A), SW7.1
unnamed: D8.2 (A), SW8.1
unnamed: D9.2 (A), SW9.1
unnamed: D10.2 (A), SW10.1
unnamed: D11.2 (A), SW11.1
unnamed: U1.5 (PA8_A4_D4_SDA), U2.2 (SDA)
unnamed: U1.6 (PA9_A5_D5_SCL), U2.1 (SCL)

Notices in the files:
hackpads/speedpad/pcb/hackpad.kicad_pcb:
©SpeedyGo55
